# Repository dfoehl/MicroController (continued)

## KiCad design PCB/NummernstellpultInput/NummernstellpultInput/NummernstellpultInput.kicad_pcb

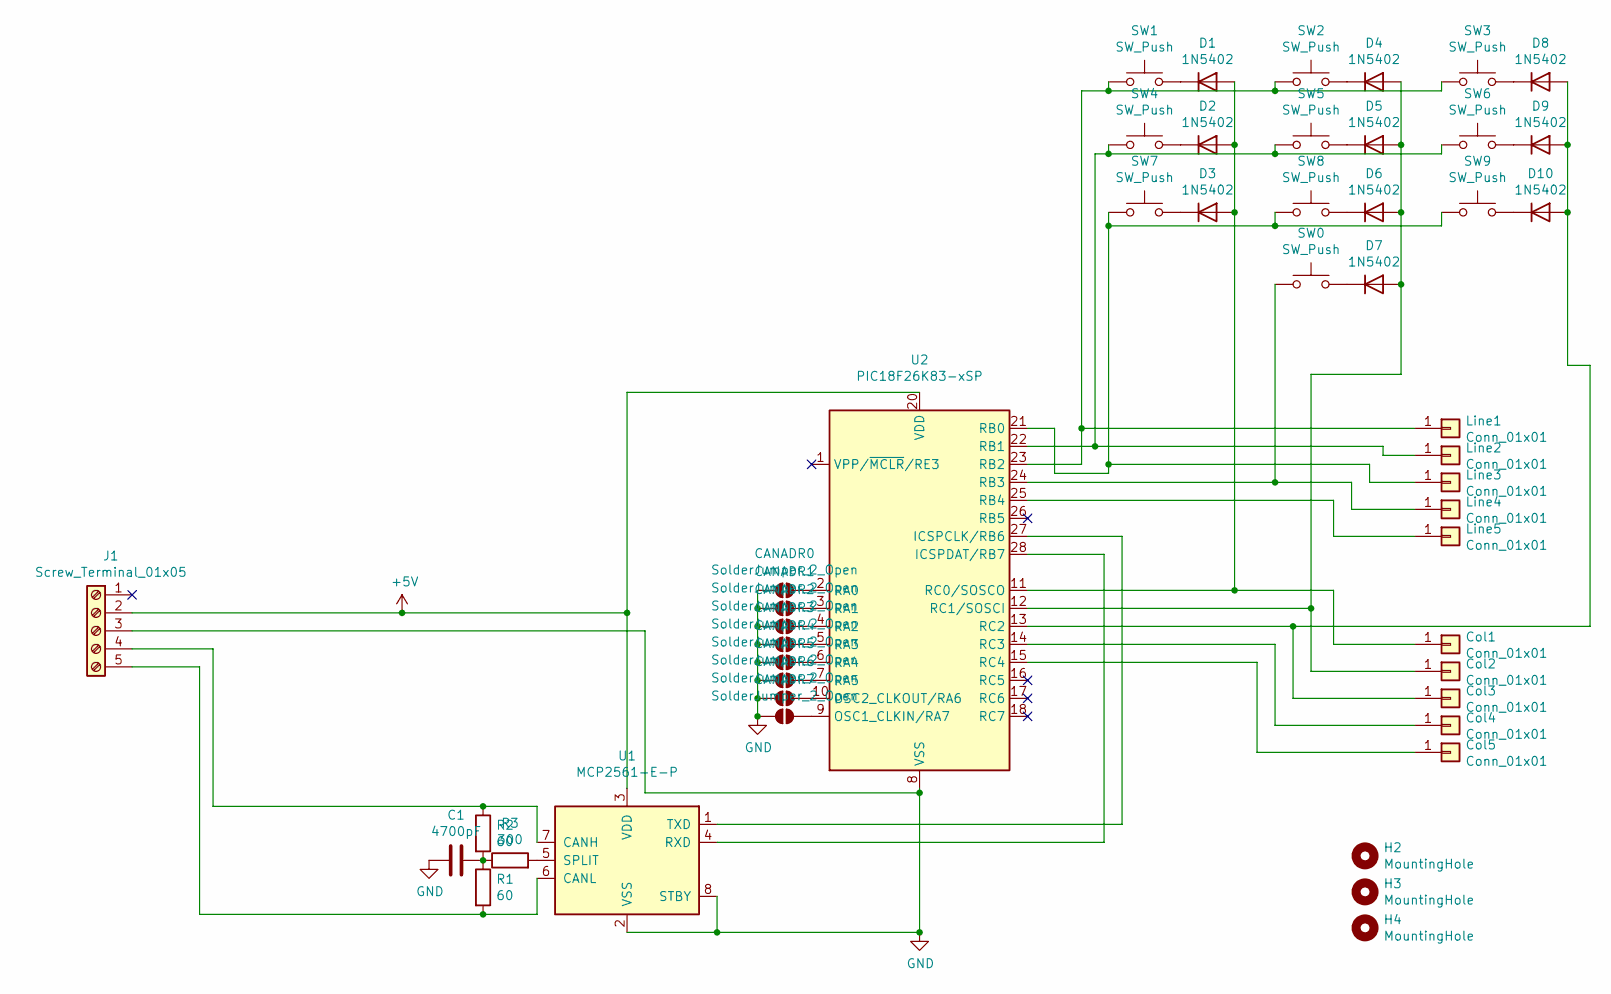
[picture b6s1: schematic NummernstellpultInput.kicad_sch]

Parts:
C1: 4700pF; C_Disc_D11.0mm_W5.0mm_P5.00mm
CANADR0, CANADR1, CANADR2, CANADR3, CANADR4, CANADR5, CANADR6, CANADR7: SolderJumper_2_Open; SolderJumper-2_P1.3mm_Open_RoundedPad1.0x1.5mm
Col1, Col2, Col3, Col4, Col5: Conn_01x01; SolderWirePad_1x01_SMD_5x10mm
D1, D2, D3, D4, D5, D6, D7, D8, D9, D10: 1N5402; D_SMB_Handsoldering
H2, H3, H4: MountingHole; MountingHole_3.5mm_Pad
J1: Screw_Terminal_01x05; TerminalBlock_RND_205-00235_1x05_P5.08mm_Horizontal
Line1, Line2, Line3, Line4, Line5: Conn_01x01; SolderWirePad_1x01_SMD_5x10mm
R1, R2: 60; R_Axial_DIN0207_L6.3mm_D2.5mm_P10.16mm_Horizontal
R3: 300; R_Axial_DIN0207_L6.3mm_D2.5mm_P10.16mm_Horizontal
SW0, SW1, SW2, SW3, SW4, SW5, SW6, SW7, SW8, SW9: SW_Push; SW_Cherry_MX_1.00u_Plate
U1: MCP2561-E-P; DIP-8_W7.62mm
U2: PIC18F26K83-xSP; DIP-28_W7.62mm

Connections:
+5V: J1.2, U1.3 (VDD), U2.20 (VDD)
GND: C1.1, CANADR0.1 (A), CANADR1.1 (A), CANADR2.1 (A), CANADR3.1 (A), CANADR4.1 (A), CANADR5.1 (A), CANADR6.1 (A), CANADR7.1 (A), J1.3, U1.2 (VSS), U1.8 (STBY), U2.8 (VSS), U2.19 (VSS)
unnamed: C1.2, R1.1, R2.2, R3.1
unnamed: CANADR0.2 (B), U2.2 (RA0)
unnamed: CANADR1.2 (B), U2.3 (RA1)
unnamed: CANADR2.2 (B), U2.4 (RA2)
unnamed: CANADR3.2 (B), U2.5 (RA3)
unnamed: CANADR4.2 (B), U2.6 (RA4)
unnamed: CANADR5.2 (B), U2.7 (RA5)
unnamed: CANADR6.2 (B), U2.10 (OSC2_CLKOUT/RA6)
unnamed: CANADR7.2 (B), U2.9 (OSC1_CLKIN/RA7)
unnamed: Col1.1, D1.2 (A), D2.2 (A), D3.2 (A), U2.11 (RC0/SOSCO)
unnamed: Col2.1, D4.2 (A), D5.2 (A), D6.2 (A), D7.2 (A), U2.12 (RC1/SOSCI)
unnamed: Col3.1, D8.2 (A), D9.2 (A), D10.2 (A), U2.13 (RC2)
unnamed: Col4.1, U2.14 (RC3)
unnamed: Col5.1, U2.15 (RC4)
unnamed: D1.1 (K), SW1.2
unnamed: D2.1 (K), SW4.2
unnamed: D3.1 (K), SW7.2
unnamed: D4.1 (K), SW2.2
unnamed: D5.1 (K), SW5.2
unnamed: D6.1 (K), SW8.2
unnamed: D7.1 (K), SW0.2
unnamed: D8.1 (K), SW3.2
unnamed: D9.1 (K), SW6.2
unnamed: D10.1 (K), SW9.2
unnamed: J1.4, R2.1, U1.7 (CANH)
unnamed: J1.5, R1.2, U1.6 (CANL)
unnamed: Line1.1, SW1.1, SW2.1, SW3.1, U2.23 (RB2)
unnamed: Line2.1, SW4.1, SW5.1, SW6.1, U2.22 (RB1)
unnamed: Line3.1, SW7.1, SW8.1, SW9.1, U2.21 (RB0)
unnamed: Line4.1, SW0.1, U2.24 (RB3)
unnamed: Line5.1, U2.25 (RB4)
unnamed: U1.4 (RXD), U2.28 (ICSPDAT/RB7)
unnamed: R3.2, U1.5 (SPLIT)
unnamed: U1.1 (TXD), U2.27 (ICSPCLK/RB6)

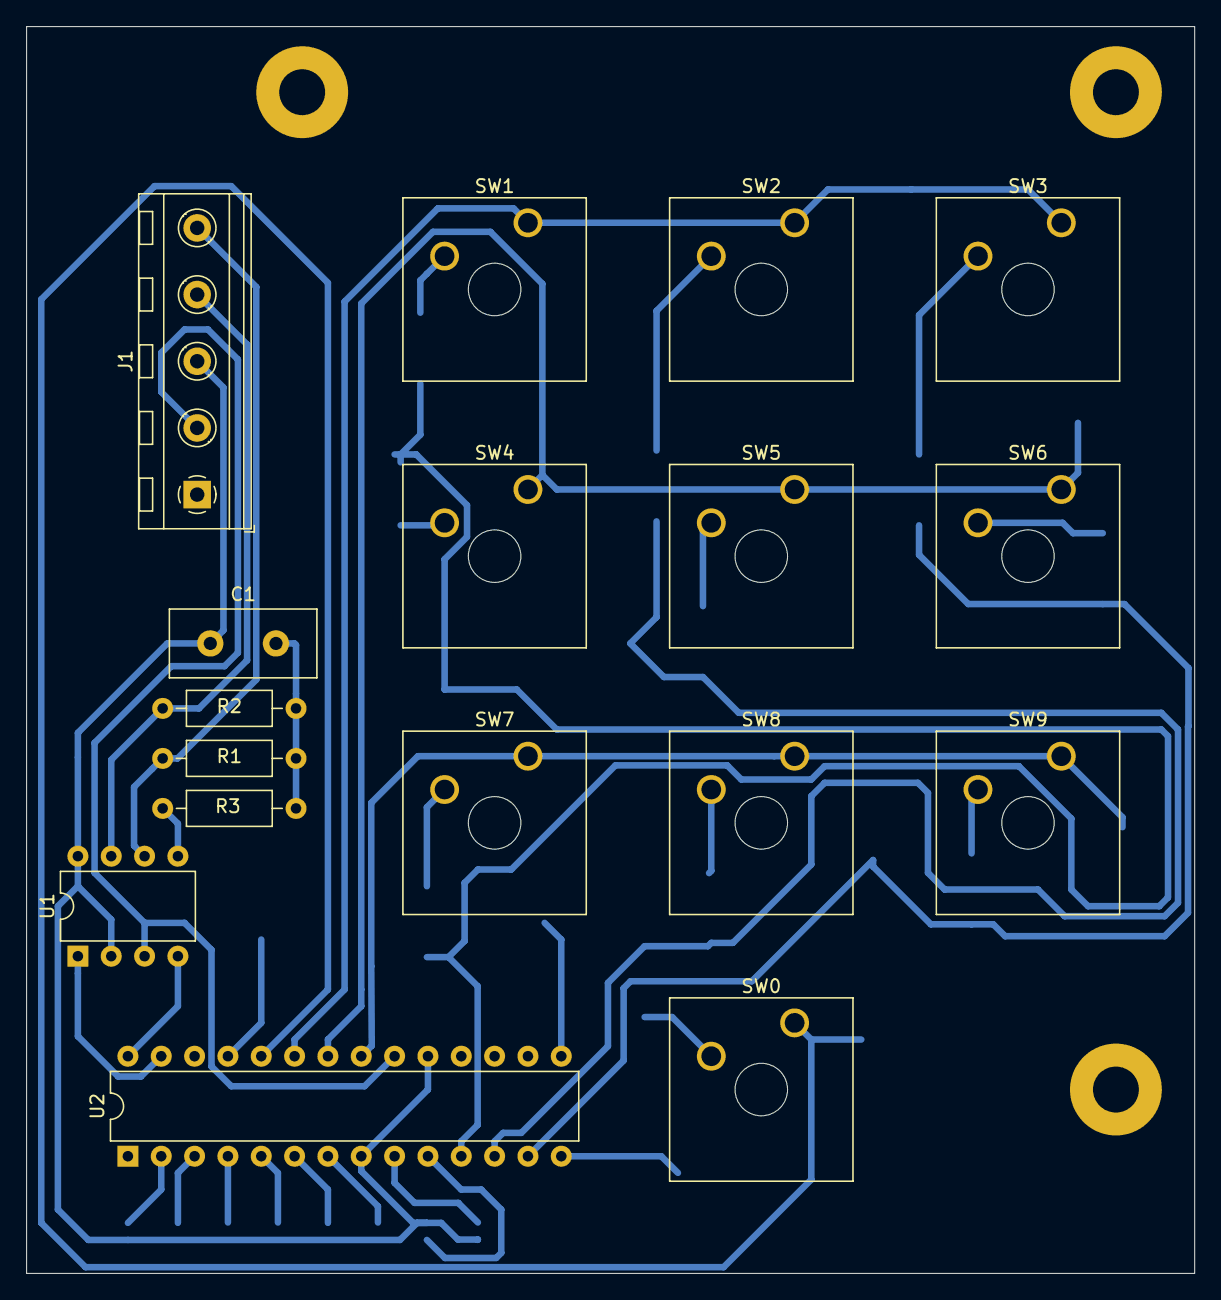
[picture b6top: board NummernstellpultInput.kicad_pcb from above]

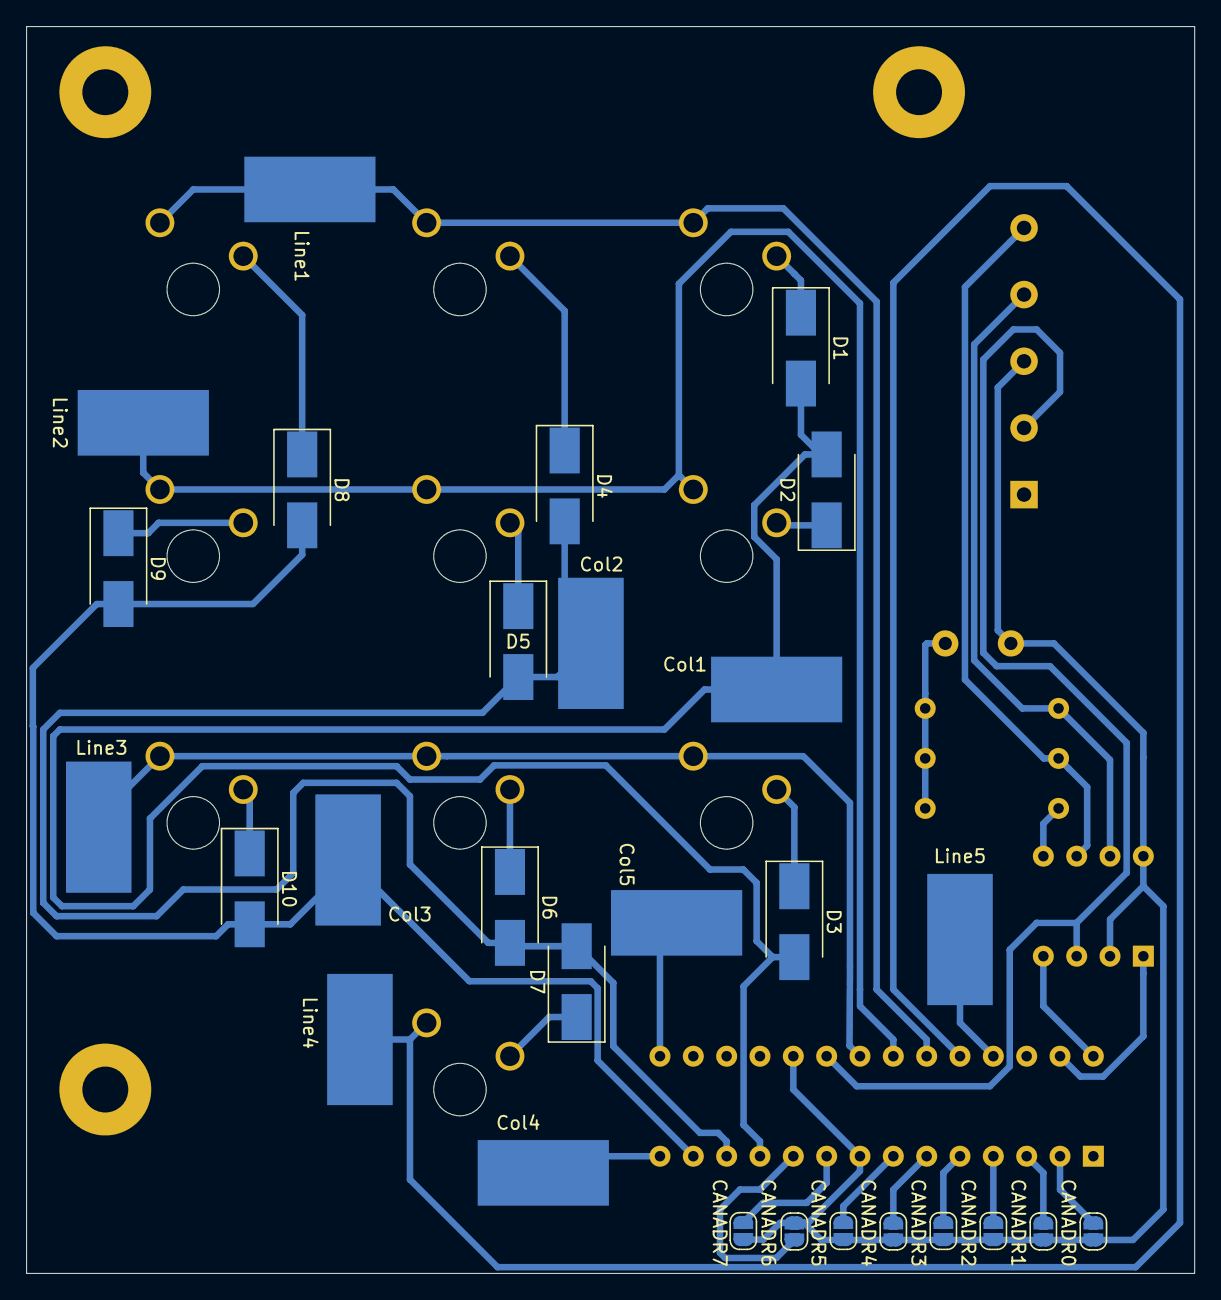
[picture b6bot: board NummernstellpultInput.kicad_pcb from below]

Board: 2 copper layers, 89.0 x 95.0 mm, 48 parts (28 on the bottom side), 36 nets.

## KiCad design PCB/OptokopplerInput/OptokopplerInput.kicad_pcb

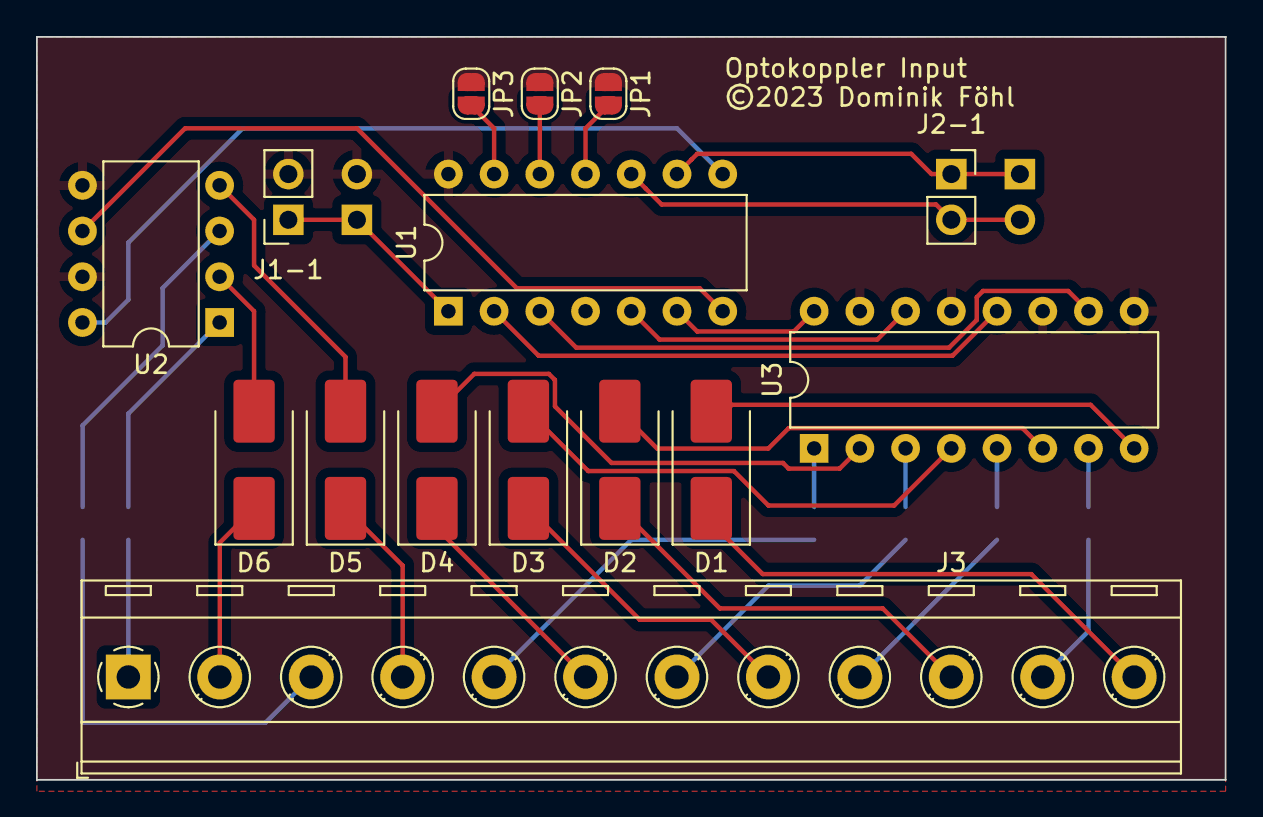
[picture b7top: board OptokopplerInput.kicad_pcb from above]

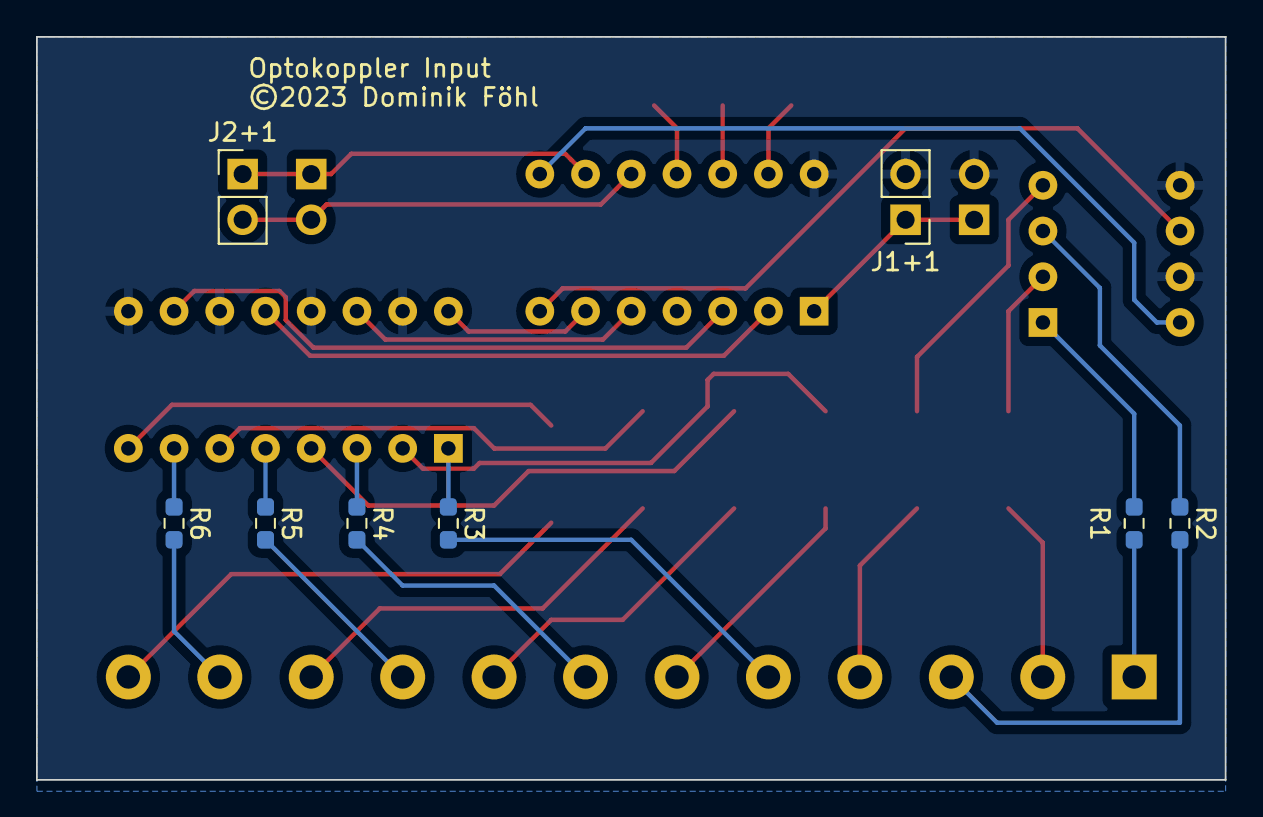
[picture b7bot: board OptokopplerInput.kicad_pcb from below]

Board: 2 copper layers, 66.0 x 41.3 mm, 23 parts (8 on the bottom side), 37 nets.

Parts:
D1, D2, D3, D4, D5, D6: 1N4001; D_SMB_Handsoldering
J1+1: Power; PinHeader_1x02_P2.54mm_Vertical
J1-1: Power; PinSocket_1x02_P2.54mm_Vertical
J2+1: I2C; PinHeader_1x02_P2.54mm_Vertical
J2-1: I2C; PinSocket_1x02_P2.54mm_Vertical
J3: Screw_Terminal_01x12; TerminalBlock_RND_205-00297_1x12_P5.08mm_Horizontal
JP1: I2C Bit 1; SolderJumper-2_P1.3mm_Open_RoundedPad1.0x1.5mm
JP2: I2C Bit 2; SolderJumper-2_P1.3mm_Open_RoundedPad1.0x1.5mm
JP3: I2C Bit 3; SolderJumper-2_P1.3mm_Open_RoundedPad1.0x1.5mm
R1, R2, R3, R4, R5, R6: 1000; R_0603_1608Metric_Pad0.98x0.95mm_HandSolder
U1: PIC16F1503-IP; DIP-14_W7.62mm
U2: LTV-825; DIP-8_W7.62mm
U3: LTV-845; DIP-16_W7.62mm

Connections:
+5V: J1+1.1, J1-1.1, U1.1 (VDD)
GND: J1+1.2, J1-1.2, JP1.1 (A), JP2.1 (A), JP3.1 (A), U1.14 (VSS), U2.5, U2.7, U3.9, U3.11, U3.13, U3.15
unnamed: D1.2 (A), U3.8
unnamed: D1.1 (K), J3.12
unnamed: D2.2 (A), U3.6
unnamed: D2.1 (K), J3.10
unnamed: D3.2 (A), U3.4
unnamed: D3.1 (K), J3.8
unnamed: D4.2 (A), U3.2
unnamed: D4.1 (K), J3.6
unnamed: D5.2 (A), U2.4
unnamed: D5.1 (K), J3.4
unnamed: D6.2 (A), U2.2
unnamed: D6.1 (K), J3.2
unnamed: J2+1.1, J2-1.1, U1.9 (SDI/SDA/PWM4/NCO1/C2IN1-/C1IN1-/AN5/RC1)
unnamed: J2+1.2, J2-1.2, U1.10 (SCK/SCL/CLC2/C2IN+/AN4/RC0)
unnamed: J3.1, R1.2
unnamed: J3.3, R2.2
unnamed: J3.5, R3.2
unnamed: J3.7, R4.2
unnamed: J3.9, R5.2
unnamed: J3.11, R6.2
unnamed: JP1.2 (B), U1.11 (RA2/AN2/DACOUT2/C1OUT/T0CKI/~CWG1FLT/CL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)
unnamed: JP2.2 (B), U1.12 (RA1/AN1/Vref+/C1IN0-/C2IN0-/ICSPCLK)
unnamed: JP3.2 (B), U1.13 (RA0/AN0/DACOUT1/C1IN+/ICSPDAT)
unnamed: R1.1, U2.1
unnamed: R2.1, U2.3
unnamed: R3.1, U3.1
unnamed: R4.1, U3.3
unnamed: R5.1, U3.5
unnamed: R6.1, U3.7
unnamed: U1.6 (CLC2IN1/CWG1B/C2OUT/RC4), U3.16
unnamed: U1.5 (PWM1/CLC1/CWG1A/RC5), U3.14
unnamed: U1.3 (RA4/AN3/T1G/NCO1/SDO/CLKOUT), U3.10
unnamed: U1.2 (RA5/T1CKI/NCO1CLK/CLCIN1/CLKIN), U3.12
unnamed: U1.8 (SDO/C2IN2-/C1IN2-/AN6/RC2), U2.8
unnamed: U1.7 (~SS/PWM2/CLCIN0/C2IN3-/C1IN3-/AN7/RC3), U2.6

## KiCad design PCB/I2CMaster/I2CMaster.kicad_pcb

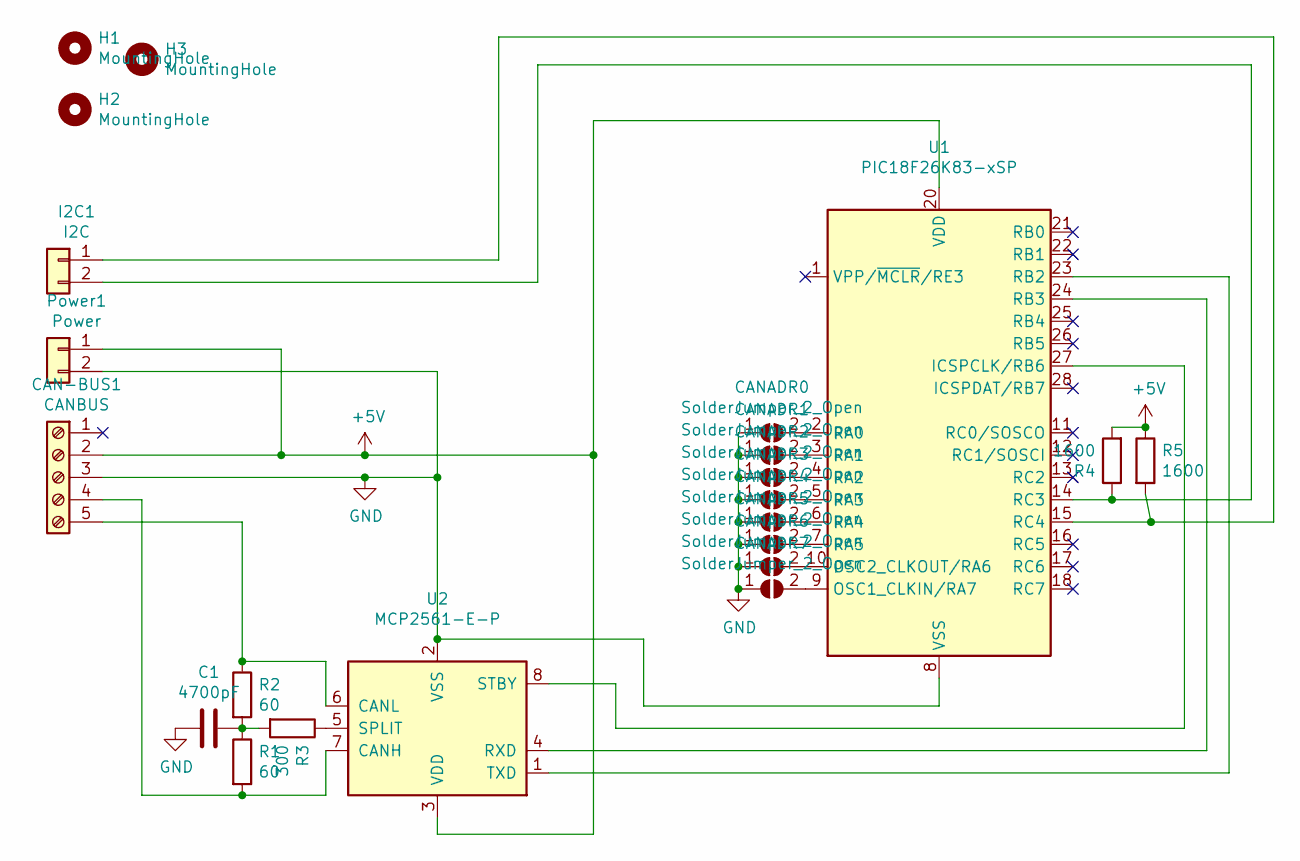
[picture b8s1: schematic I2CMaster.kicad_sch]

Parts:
C1: 4700pF; C_Disc_D11.0mm_W5.0mm_P5.00mm
CAN-BUS1: CANBUS; TerminalBlock_RND_205-00235_1x05_P5.08mm_Horizontal
CANADR0, CANADR1, CANADR2, CANADR3, CANADR4, CANADR5, CANADR6, CANADR7: SolderJumper_2_Open; SolderJumper-2_P1.3mm_Open_RoundedPad1.0x1.5mm
H1, H2, H3: MountingHole; MountingHole_3.5mm_Pad
I2C1: I2C; PinHeader_2x01_P2.54mm_Horizontal
Power1: Power; PinHeader_2x01_P2.54mm_Horizontal
R1, R2: 60; R_Axial_DIN0207_L6.3mm_D2.5mm_P10.16mm_Horizontal
R3: 300; R_Axial_DIN0207_L6.3mm_D2.5mm_P10.16mm_Horizontal
R4, R5: 1600; R_0603_1608Metric_Pad1.05x0.95mm_HandSolder
U1: PIC18F26K83-xSP; DIP-28_W7.62mm
U2: MCP2561-E-P; DIP-8_W7.62mm

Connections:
+5V: CAN-BUS1.2, Power1.1, R4.2, R5.1, U1.20 (VDD), U2.3 (VDD)
GND: C1.2, CAN-BUS1.3, CANADR0.1 (A), CANADR1.1 (A), CANADR2.1 (A), CANADR3.1 (A), CANADR4.1 (A), CANADR5.1 (A), CANADR6.1 (A), CANADR7.1 (A), Power1.2, U1.8 (VSS), U1.19 (VSS), U2.2 (VSS)
unnamed: C1.1, R1.1, R2.2, R3.2
unnamed: CAN-BUS1.4, R1.2, U2.7 (CANH)
unnamed: CAN-BUS1.5, R2.1, U2.6 (CANL)
unnamed: CANADR0.2 (B), U1.2 (RA0)
unnamed: CANADR1.2 (B), U1.3 (RA1)
unnamed: CANADR2.2 (B), U1.4 (RA2)
unnamed: CANADR3.2 (B), U1.5 (RA3)
unnamed: CANADR4.2 (B), U1.6 (RA4)
unnamed: CANADR5.2 (B), U1.7 (RA5)
unnamed: CANADR6.2 (B), U1.10 (OSC2_CLKOUT/RA6)
unnamed: CANADR7.2 (B), U1.9 (OSC1_CLKIN/RA7)
unnamed: I2C1.1, R5.2, U1.15 (RC4)
unnamed: I2C1.2, R4.1, U1.14 (RC3)
unnamed: U1.27 (ICSPCLK/RB6), U2.8 (STBY)
unnamed: U1.23 (RB2), U2.1 (TXD)
unnamed: U1.24 (RB3), U2.4 (RXD)
unnamed: R3.1, U2.5 (SPLIT)

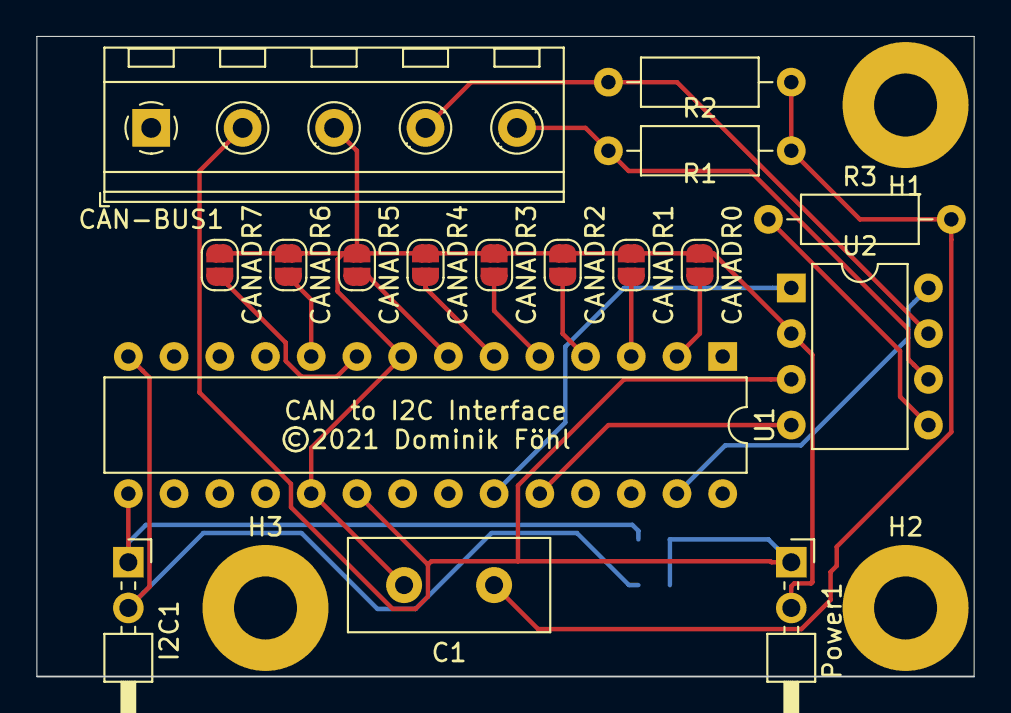
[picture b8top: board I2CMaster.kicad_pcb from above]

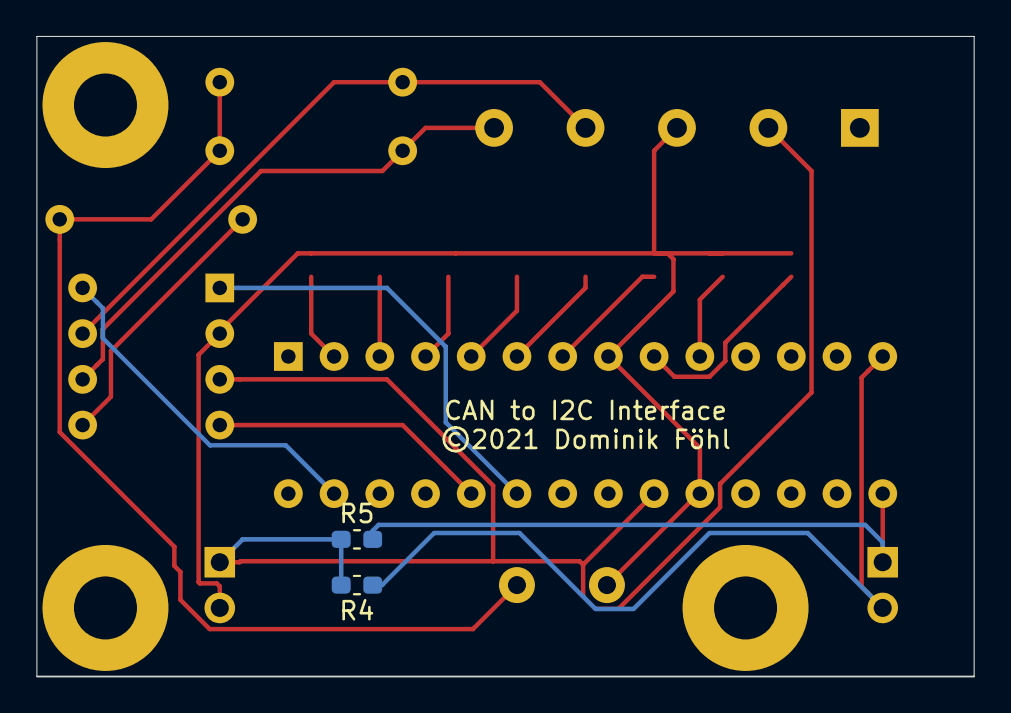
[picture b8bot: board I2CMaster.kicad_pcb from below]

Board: 2 copper layers, 52.1 x 35.5 mm, 22 parts (2 on the bottom side), 19 nets.

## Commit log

2020-04-21 Initial commit of IC code and PCB Info
2020-05-12 Added two new signal states: HP0Sh1 and HP0X
2020-06-12 Added CAN2I2C Project
2020-10-02 Added HP00 and HP00X
2020-10-02 Changed I2C Pins
2020-10-02 .gitignore angepasst PCB Dateien hinzugefügt Can2Rest Webservice hinzugefügt
2020-10-02 Added OutputComtroller
2022-06-23 Bump Newtonsoft.Json from 12.0.3 to 13.0.1 in /Can2Rest/CanClient
    Bumps [Newtonsoft.Json](https://github.com/JamesNK/Newtonsoft.Json) from 12.0.3 to 13.0.1.
    - [Release notes](https://github.com/JamesNK/Newtonsoft.Json/releases)
    - [Commits](https://github.com/JamesNK/Newtonsoft.Json/compare/12.0.3...13.0.1)
    ---
    updated-dependencies:
    - dependency-name: Newtonsoft.Json
2022-12-08 Bump Newtonsoft.Json from 12.0.3 to 13.0.2 in /Can2Rest/CanClient
    Bumps [Newtonsoft.Json](https://github.com/JamesNK/Newtonsoft.Json) from 12.0.3 to 13.0.2.
    - [Release notes](https://github.com/JamesNK/Newtonsoft.Json/releases)
    - [Commits](https://github.com/JamesNK/Newtonsoft.Json/compare/12.0.3...13.0.2)
    ---
    updated-dependencies:
    - dependency-name: Newtonsoft.Json
2023-11-12 Remove ignored files.
2023-11-12 Added Input module.
2023-11-12 Tuned .gitignore.
2023-11-12 File cleanup.
2023-11-12 Fixes for output module.
2023-11-12 Added NumberControl Input and Display.
2023-11-18 Updated Can2Rest to dotnet 8.
2023-11-18 Fix Bug in Can2Rest.
2023-11-18 Changed data request logic for CAN-Bus.
2023-12-04 First try
2023-12-05 Fixed wrong value read bug.
2024-04-28 Switch from MOC3041 to Relay.
2024-09-05 Update PCBs and add track occupation PCB.
2024-09-05 Dump current status.
2024-12-04 Added new PCB and updated older ones.
2024-12-04 Added Timed Starter µC.
